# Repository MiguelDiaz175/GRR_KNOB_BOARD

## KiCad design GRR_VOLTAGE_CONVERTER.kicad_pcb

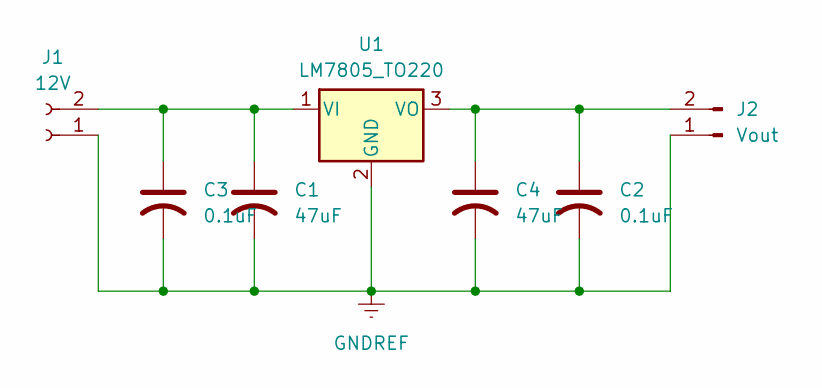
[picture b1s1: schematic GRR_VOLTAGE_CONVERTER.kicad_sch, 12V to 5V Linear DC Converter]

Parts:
C1, C4: 47uF; C_Radial_D5.0mm_H5.0mm_P2.00mm
C2, C3: 0.1uF; C_0805_2012Metric_Pad1.18x1.45mm_HandSolder
J1: 12V; TerminalBlock_Phoenix_MKDS-1,5-2-5.08_1x02_P5.08mm_Horizont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
J2: Vout; TerminalBlock_Phoenix_MKDS-1,5-2-5.08_1x02_P5.08mm_Horizont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
U1: LM7805_TO220; TO-220-3_Vertical

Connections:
GNDREF: C1.2, C2.2, C3.2, C4.2, J1.1, J2.1, U1.2 (GND)
unnamed: C1.1, C3.1, J1.2, U1.1 (VI)
unnamed: C2.1, C4.1, J2.2, U1.3 (VO)

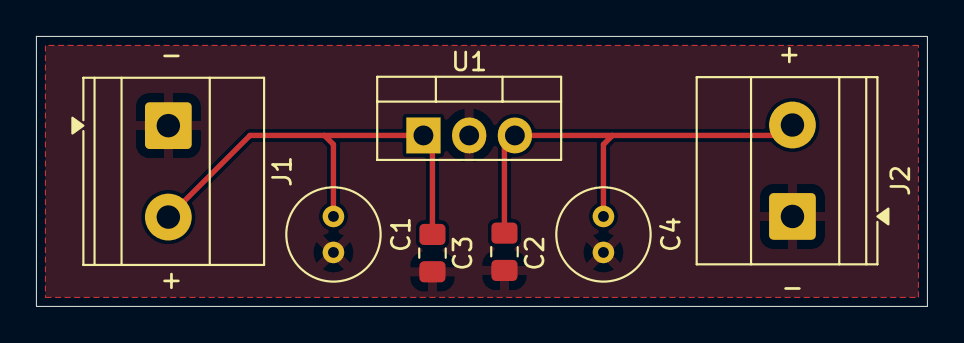
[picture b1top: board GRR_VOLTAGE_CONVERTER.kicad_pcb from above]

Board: 2 copper layers, 49.5 x 15.0 mm, 7 parts (0 on the bottom side), 3 nets.

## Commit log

2025-10-15 Create KiKad
2025-10-15 Add files via upload
    made 12V->3V3 regulator
2025-10-15 12V -> 3V3 regulator
2025-10-21 Updated PCB for knob board
    Im pretty sure that the only thing that needs to be added to the schematic is the connector for the motor which will be connected to CANH and CANL. Then footprints will need to be assigned
2025-10-23 CORRECTED_KNOB_BOARD_UPDATED
2025-10-23 Updated Knob Board
